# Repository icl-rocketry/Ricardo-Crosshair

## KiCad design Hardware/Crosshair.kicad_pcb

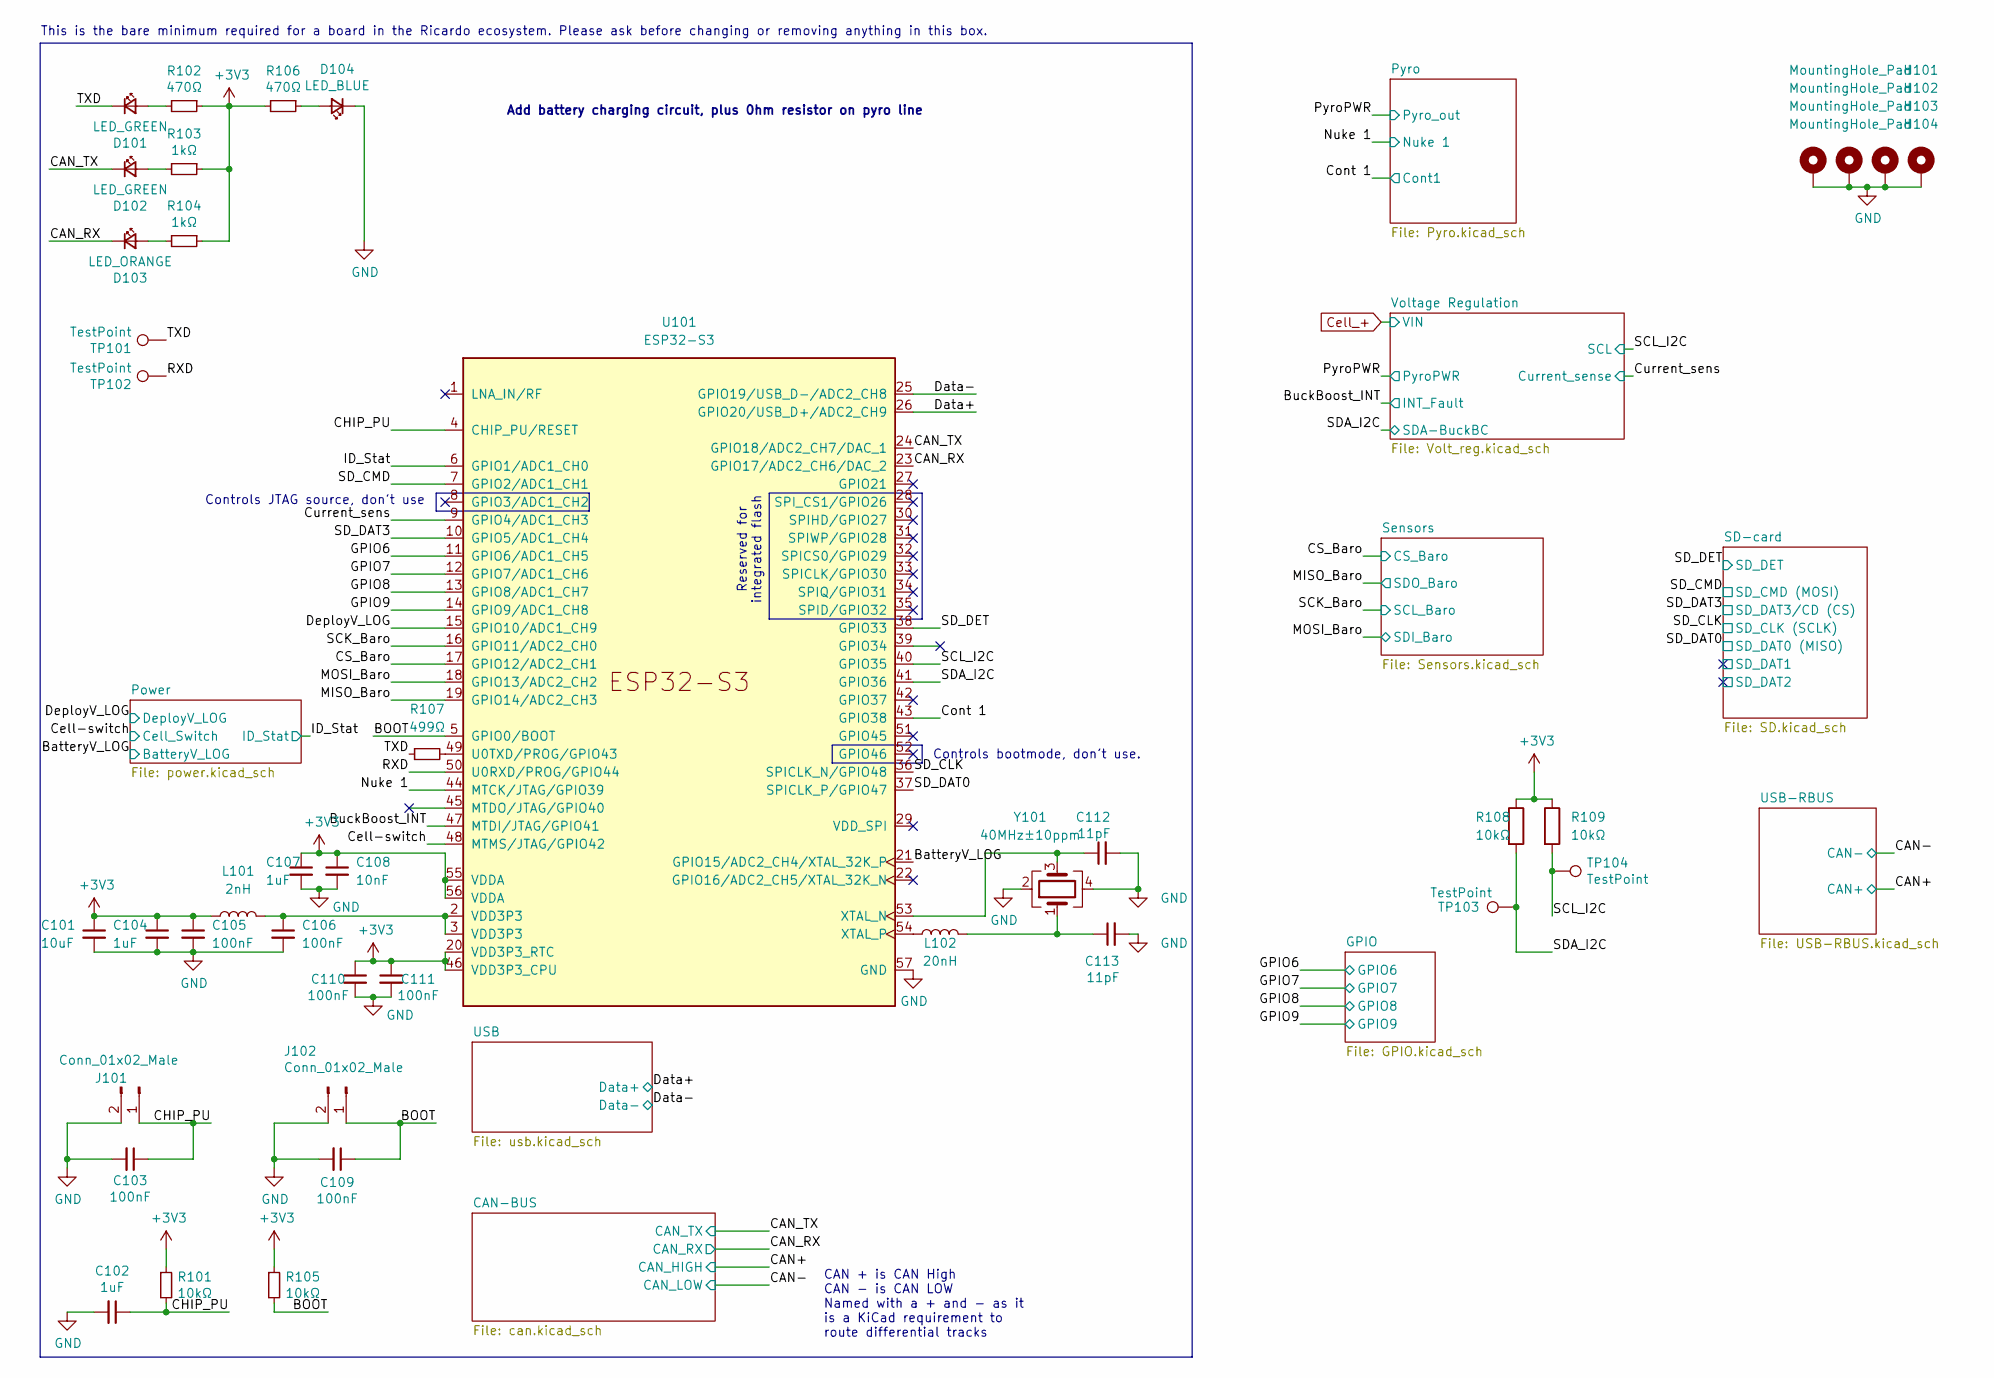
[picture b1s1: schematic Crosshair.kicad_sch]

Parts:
C101: 10uF; C_0402_1005Metric
C102, C104, C107: 1uF; C_0402_1005Metric
C103, C105, C106, C109, C110, C111: 100nF; C_0402_1005Metric
C108: 10nF; C_0402_1005Metric
C112, C113: 11pF; C_0402_1005Metric
D101, D102: LED_GREEN; LED_0402_1005Metric
D103: LED_ORANGE; LED_0402_1005Metric
D104: LED_BLUE; LED_0402_1005Metric
H101, H102, H103, H104: MountingHole_Pad; MountingHole_3.2mm_M3_DIN965_Pad
J101, J102: Conn_01x02_Male; PinHeader_1x02_P2.54mm_Vertical
L101: 2nH; L_0402_1005Metric
L102: 20nH; L_0402_1005Metric
R101, R105, R108, R109: 10kΩ; R_0402_1005Metric
R102, R106: 470Ω; R_0402_1005Metric
R103, R104: 1kΩ; R_0402_1005Metric
R107: 499Ω; R_0402_1005Metric
TP101, TP102, TP103, TP104: TestPoint; TestPoint_Pad_D1.0mm
U101: ESP32-S3; QFN40P700X700X90-57N
Y101: 40MHz±10ppm; Crystal_SMD_2016-4Pin_2.0x1.6mm; MPN R940000171

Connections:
+3V3: C101.1, C104.1, C105.1, C107.1, C108.1, C110.1, C111.1, L101.1, R101.1, R102.1, R103.1, R104.1, R105.1, R106.2, R108.1, R109.1, U101.20 (VDD3P3_RTC), U101.46 (VDD3P3_CPU), U101.55 (VDDA), U101.56 (VDDA); also elsewhere on the board
/BOOT: C109.1, J102.1, R105.2, U101.5 (GPIO0/BOOT)
/BatteryV_LOG: U101.21 (GPIO15/ADC2_CH4/XTAL_32K_P); also elsewhere on the board
/BuckBoost_INT: U101.47 (MTDI/JTAG/GPIO41); also elsewhere on the board
/CAN_RX: D103.1 (K), U101.23 (GPIO17/ADC2_CH6/DAC_2); also elsewhere on the board
/CAN_TX: D102.1 (K), U101.24 (GPIO18/ADC2_CH7/DAC_1); also elsewhere on the board
/CHIP_PU: C102.1, C103.1, J101.1, R101.2, U101.4 (CHIP_PU/RESET)
/CS_Baro: U101.17 (GPIO12/ADC2_CH1); also elsewhere on the board
/Cell-switch: U101.48 (MTMS/JTAG/GPIO42); also elsewhere on the board
/Cont 1: U101.43 (GPIO38); also elsewhere on the board
/Current_sens: U101.9 (GPIO4/ADC1_CH3); also elsewhere on the board
/Data+: U101.26 (GPIO20/USB_D+/ADC2_CH9); also elsewhere on the board
/Data-: U101.25 (GPIO19/USB_D-/ADC2_CH8); also elsewhere on the board
/DeployV_LOG: U101.15 (GPIO10/ADC1_CH9); also elsewhere on the board
/GPIO6: U101.11 (GPIO6/ADC1_CH5); also elsewhere on the board
/GPIO7: U101.12 (GPIO7/ADC1_CH6); also elsewhere on the board
/GPIO8: U101.13 (GPIO8/ADC1_CH7); also elsewhere on the board
/GPIO9: U101.14 (GPIO9/ADC1_CH8); also elsewhere on the board
/ID_Stat: U101.6 (GPIO1/ADC1_CH0); also elsewhere on the board
/MISO_Baro: U101.19 (GPIO14/ADC2_CH3); also elsewhere on the board
/MOSI_Baro: U101.18 (GPIO13/ADC2_CH2); also elsewhere on the board
/Nuke 1: U101.44 (MTCK/JTAG/GPIO39); also elsewhere on the board
/RXD: TP102.1 (1_1), U101.50 (U0RXD/PROG/GPIO44)
/SCK_Baro: U101.16 (GPIO11/ADC2_CH0); also elsewhere on the board
/SCL_I2C: R109.2, TP104.1 (1_1), U101.40 (GPIO35); also elsewhere on the board
/SDA_I2C: R108.2, TP103.1 (1_1), U101.41 (GPIO36); also elsewhere on the board
/SD_CLK: U101.36 (SPICLK_N/GPIO48); also elsewhere on the board
/SD_CMD: U101.7 (GPIO2/ADC1_CH1); also elsewhere on the board
/SD_DAT0: U101.37 (SPICLK_P/GPIO47); also elsewhere on the board
/SD_DAT3: U101.10 (GPIO5/ADC1_CH4); also elsewhere on the board
/SD_DET: U101.38 (GPIO33); also elsewhere on the board
/TXD: D101.1 (K), R107.1, TP101.1 (1_1)
GND: C101.2, C102.2, C103.2, C104.2, C105.2, C106.2, C107.2, C108.2, C109.2, C110.2, C111.2, C112.2, C113.2, D104.1 (K), H101.1 (1_1), H102.1 (1_1), H103.1 (1_1), H104.1 (1_1), J101.2, J102.2, U101.57 (GND), Y101.2, Y101.4; also elsewhere on the board
unnamed: C106.1, L101.2, U101.2 (VDD3P3), U101.3 (VDD3P3)
unnamed: C113.1, L102.2, Y101.1
unnamed: D101.2 (A), R102.2
unnamed: D102.2 (A), R103.2
unnamed: D103.2 (A), R104.2
unnamed: D104.2 (A), R106.1
unnamed: R107.2, U101.49 (U0TXD/PROG/GPIO43)
unnamed: C112.1, U101.53 (XTAL_N), Y101.3
unnamed: L102.1, U101.54 (XTAL_P)

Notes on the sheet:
Controls bootmode, don't use.
This is the bare minimum required for a board in the Ricardo ecosystem. Please ask before changing or removing anything in this box.
CAN + is CAN High CAN - is CAN LOW Named with a + and - as it is a KiCad requirement to route differential tracks
Controls JTAG source, don't use
Add battery charging circuit, plus 0hm resistor on pyro line
Reserved for integrated flash

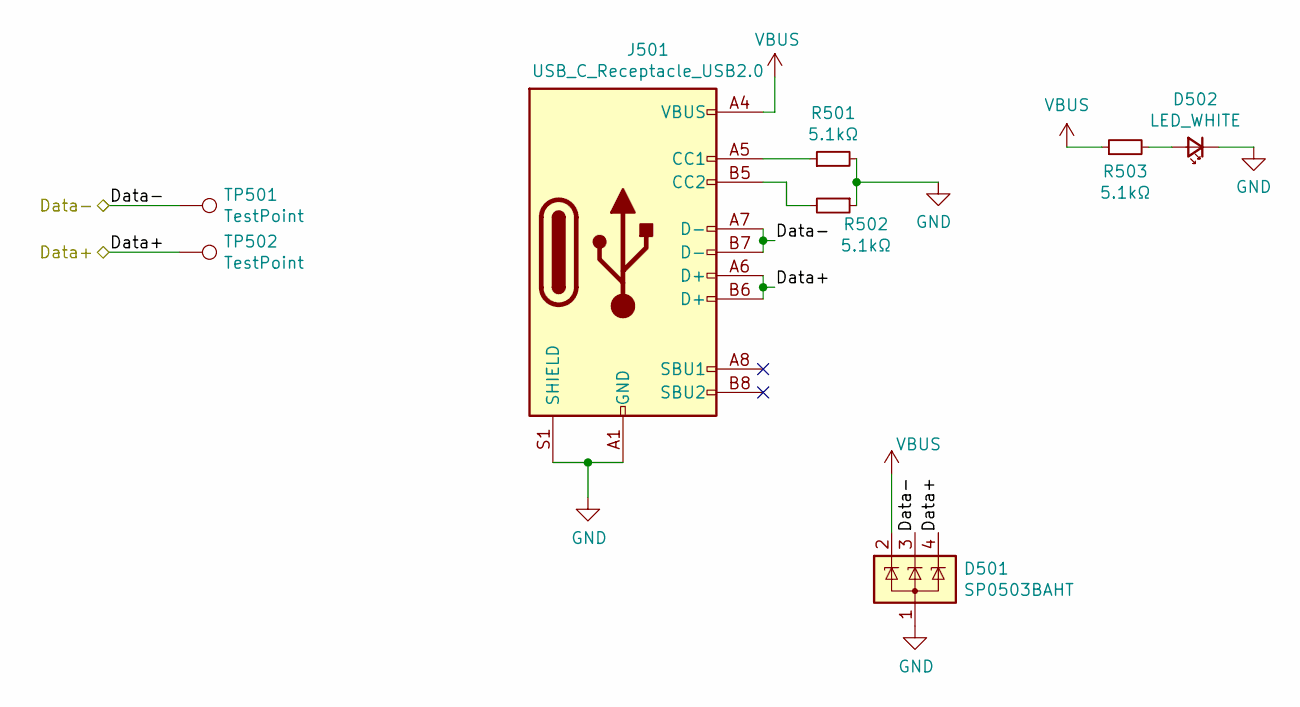
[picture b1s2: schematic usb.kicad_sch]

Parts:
D501: SP0503BAHT; SOT-143
D502: LED_WHITE; LED_0402_1005Metric
J501: USB_C_Receptacle_USB2.0; USB_C_Receptacle_Palconn_UTC16-G
R501, R502, R503: 5.1kΩ; R_0402_1005Metric
TP501, TP502: TestPoint; TestPoint_Pad_D1.0mm

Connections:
/Data+: D501.4 (K), J501.A6 (D+), J501.B6 (D+), TP502.1 (1_1); also elsewhere on the board
/Data-: D501.3 (K), J501.A7 (D-), J501.B7 (D-), TP501.1 (1_1); also elsewhere on the board
GND: D501.1 (A), D502.1 (K), J501.A1 (GND), J501.A12 (GND), J501.B1 (GND), J501.B12 (GND), J501.S1 (SHIELD), R501.2, R502.1; also elsewhere on the board
unnamed: D502.2 (A), R503.2
unnamed: J501.A5 (CC1), R501.1
unnamed: J501.B5 (CC2), R502.2
VBUS: D501.2 (K), J501.A4 (VBUS), J501.A9 (VBUS), J501.B4 (VBUS), J501.B9 (VBUS), R503.1; also elsewhere on the board

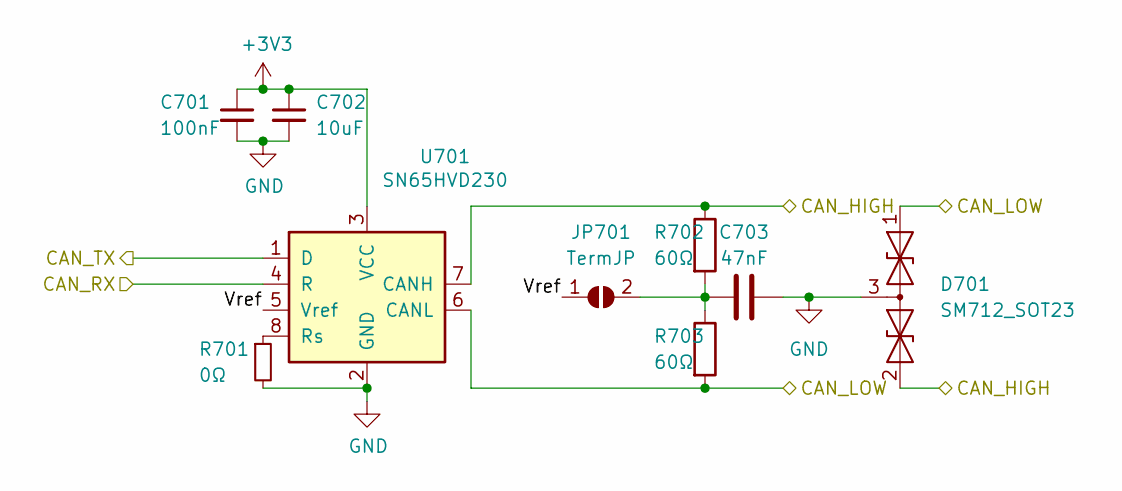
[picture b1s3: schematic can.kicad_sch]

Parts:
C701: 100nF; C_0402_1005Metric
C702: 10uF; C_0402_1005Metric
C703: 47nF; C_0402_1005Metric
D701: SM712_SOT23; SOT-23
JP701: TermJP; SolderJumper-2_P1.3mm_Open_RoundedPad1.0x1.5mm
R701: 0Ω; R_0603_1608Metric
R702, R703: 60Ω; R_0603_1608Metric
U701: SN65HVD230; SOIC-8_3.9x4.9mm_P1.27mm

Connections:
+3V3: C701.1, C702.1, U701.3 (VCC); also elsewhere on the board
/CAN+: D701.2 (A2), R702.1, U701.7 (CANH); also elsewhere on the board
/CAN-: D701.1 (A1), R703.2, U701.6 (CANL); also elsewhere on the board
/CAN-BUS/Vref: JP701.1 (A), U701.5 (Vref)
/CAN_RX: U701.4 (R); also elsewhere on the board
/CAN_TX: U701.1 (D); also elsewhere on the board
GND: C701.2, C702.2, C703.2, D701.3 (common), R701.2, U701.2 (GND); also elsewhere on the board
unnamed: C703.1, JP701.2 (B), R702.2, R703.1
unnamed: R701.1, U701.8 (Rs)

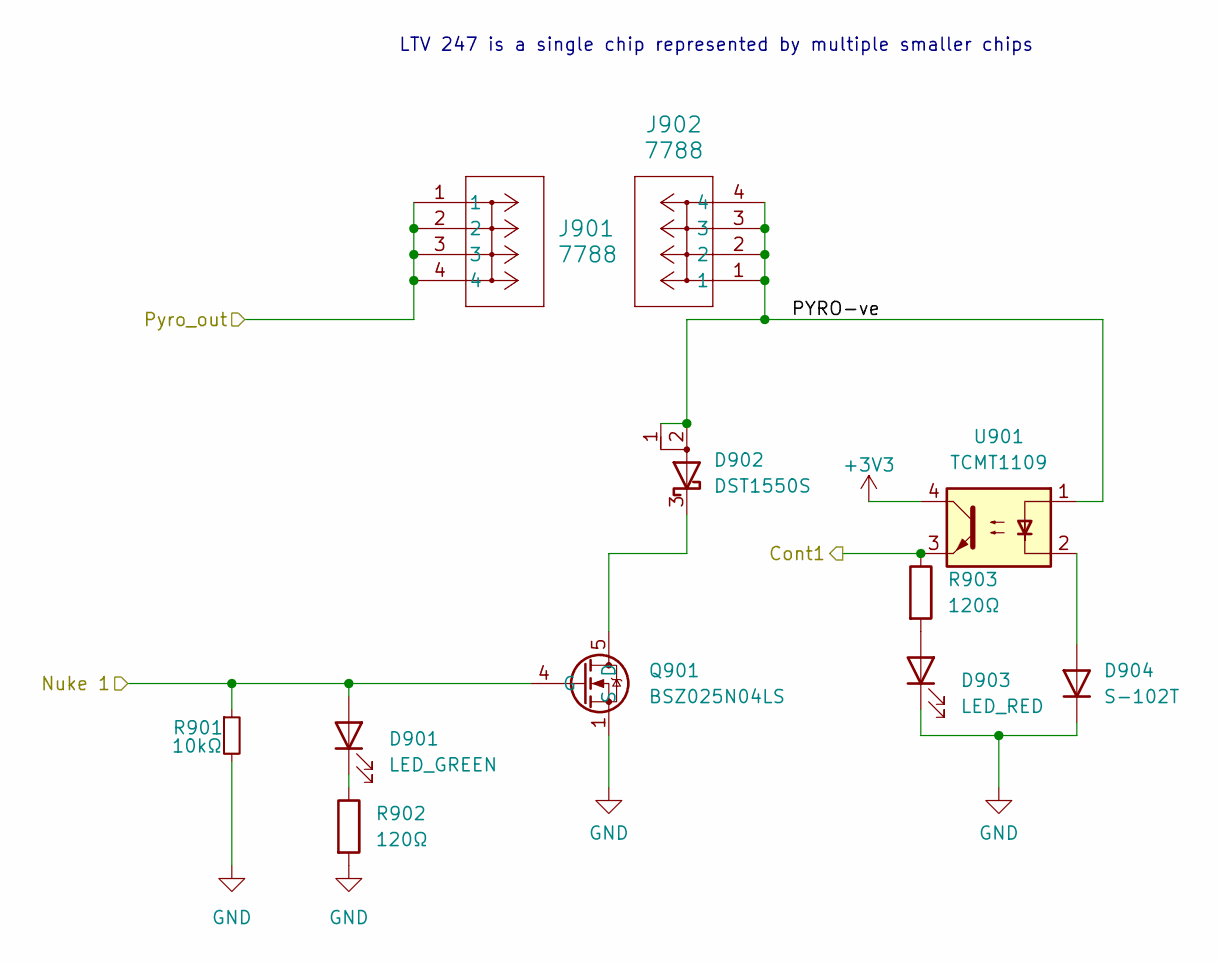
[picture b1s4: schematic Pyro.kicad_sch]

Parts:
D901: LED_GREEN; LED_0402_1005Metric
D902: DST1550S; TO-277B
D903: LED_RED; LED_0603_1608Metric
D904: S-102T; SODFL3516X70N
J901, J902: 7788; CONN_7788_KEY
Q901: BSZ025N04LS; Manufacturer_Part_Number BSZ025N04LS; Mouser Part Number 726-BSZ025N04LS
R901: 10kΩ; R_0402_1005Metric
R902: 120Ω; R_0402_1005Metric
R903: 120Ω; R_0603_1608Metric
U901: TCMT1109; SOP-4_4.4x2.6mm_P1.27mm

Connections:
+3V3: U901.4; also elsewhere on the board
/Cont 1: R903.1, U901.3; also elsewhere on the board
/Nuke 1: D901.2 (A), Q901.4 (G), R901.1; also elsewhere on the board
/Pyro/PYRO-ve: D902.1 (A), D902.2 (A), J902.1, J902.2, J902.3, J902.4, U901.1
/PyroPWR: J901.1, J901.2, J901.3, J901.4; also elsewhere on the board
GND: D903.1 (K), D904.1 (K), Q901.1 (S), Q901.2 (S), Q901.3 (S), Q901.A1 (S), R901.2, R902.2; also elsewhere on the board
unnamed: D901.1 (K), R902.1
unnamed: D902.3 (K), Q901.5 (D), Q901.6 (D), Q901.7 (D), Q901.8 (D), Q901.A5 (D)
unnamed: D903.2 (A), R903.2
unnamed: D904.2 (A), U901.2

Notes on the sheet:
LTV 247 is a single chip represented by multiple smaller chips

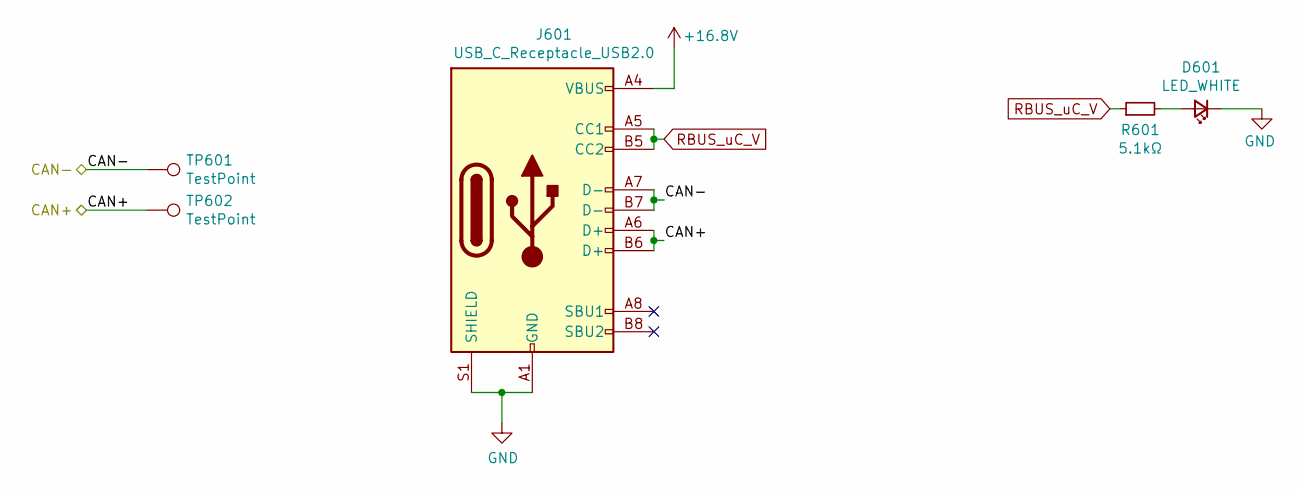
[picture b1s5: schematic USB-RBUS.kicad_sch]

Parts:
D601: LED_WHITE; LED_0402_1005Metric
J601: USB_C_Receptacle_USB2.0; USB_C_Receptacle_Palconn_UTC16-G
R601: 5.1kΩ; R_0402_1005Metric
TP601, TP602: TestPoint; TestPoint_Pad_D1.0mm

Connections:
+16.8V: J601.A4 (VBUS), J601.A9 (VBUS), J601.B4 (VBUS), J601.B9 (VBUS); also elsewhere on the board
/CAN+: J601.A6 (D+), J601.B6 (D+), TP602.1 (1_1); also elsewhere on the board
/CAN-: J601.A7 (D-), J601.B7 (D-), TP601.1 (1_1); also elsewhere on the board
GND: D601.1 (K), J601.A1 (GND), J601.A12 (GND), J601.B1 (GND), J601.B12 (GND), J601.S1 (SHIELD); also elsewhere on the board
unnamed: D601.2 (A), R601.2
RBUS_uC_V: J601.A5 (CC1), J601.B5 (CC2), R601.1; also elsewhere on the board

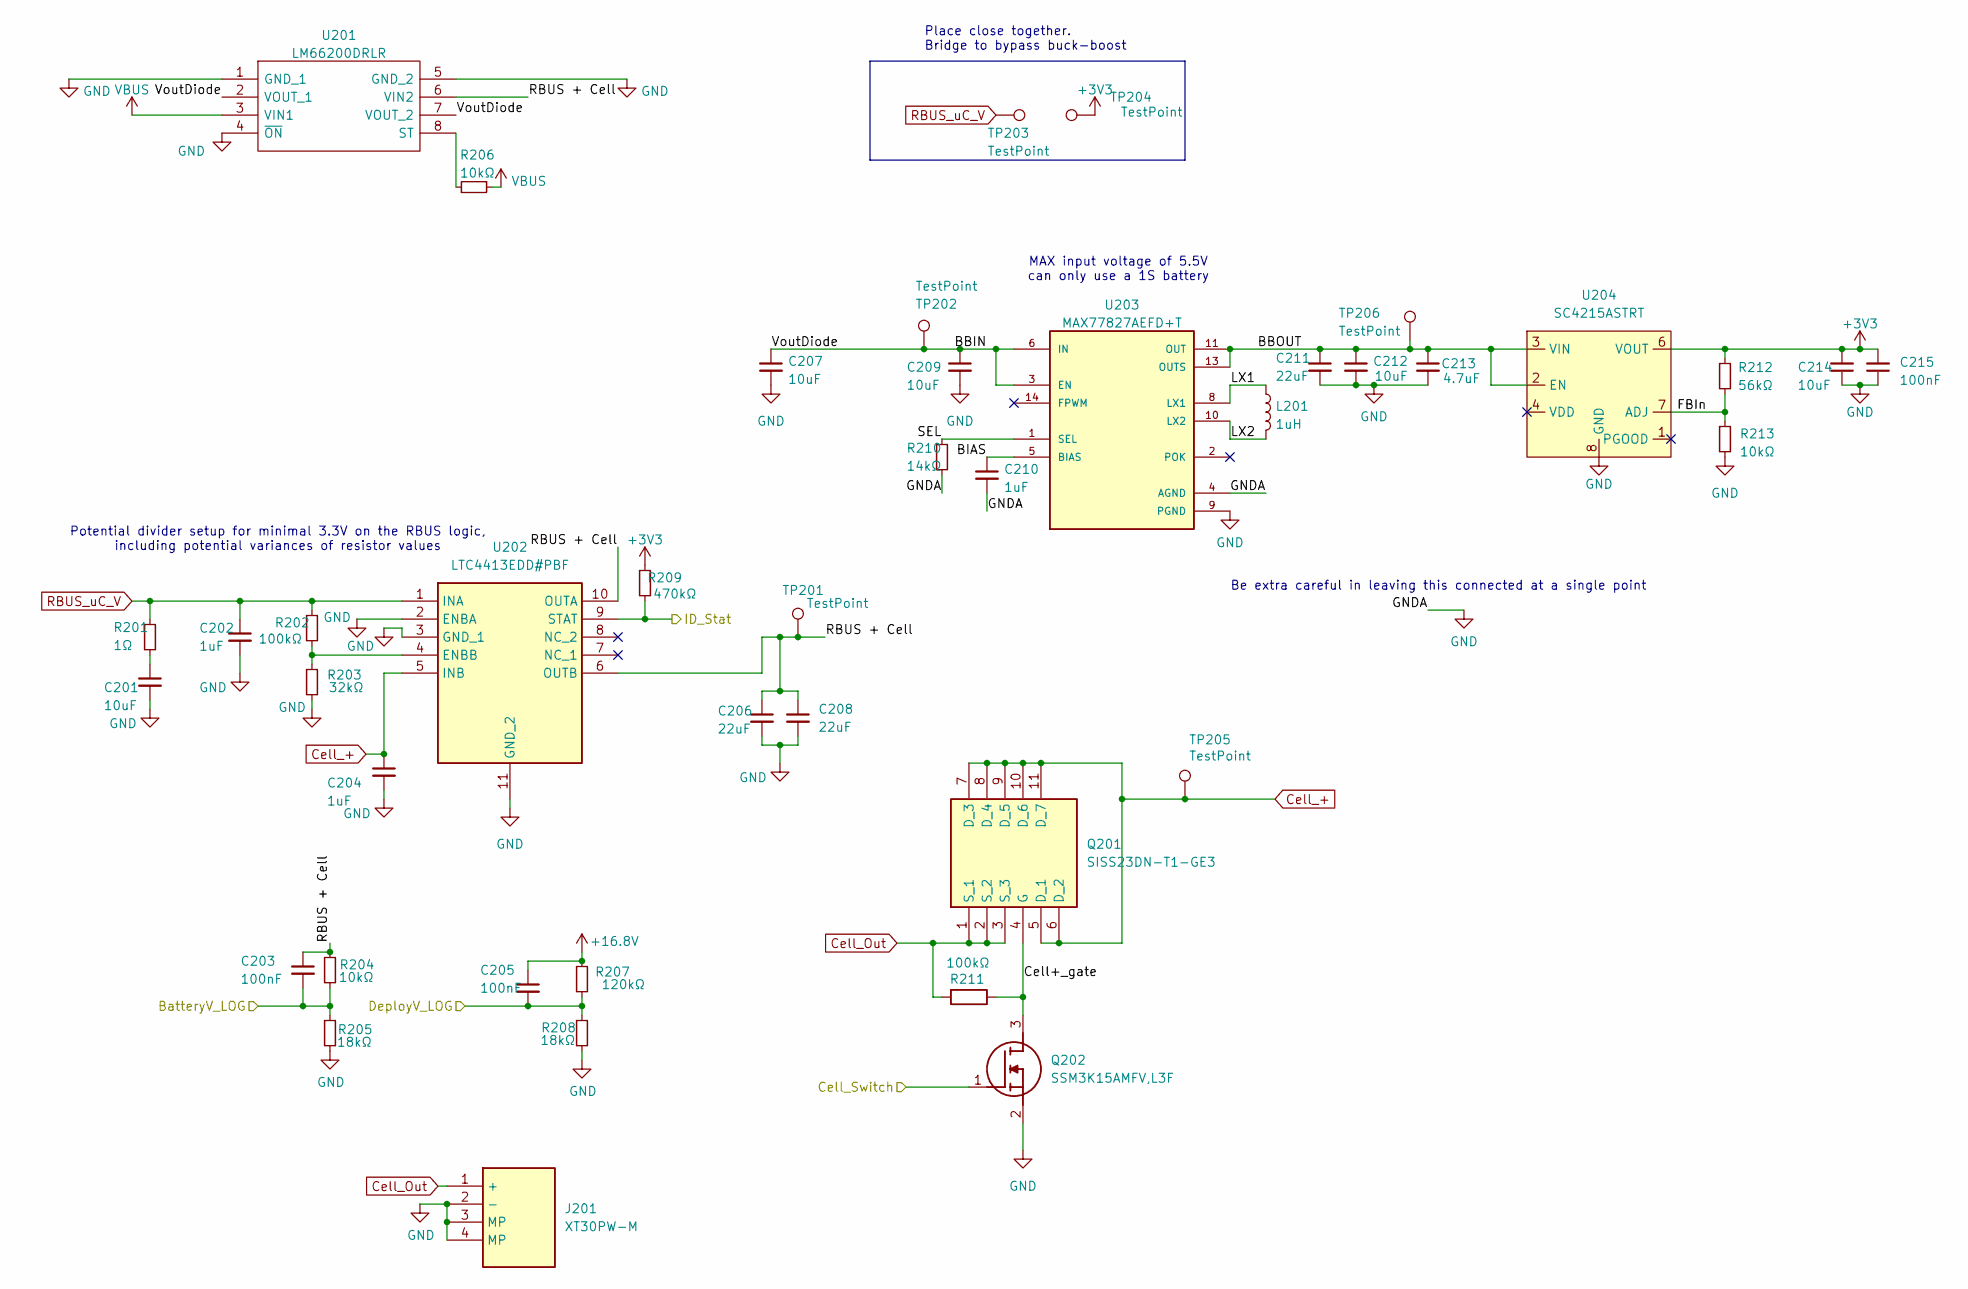
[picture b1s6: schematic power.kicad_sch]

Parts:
C201, C207, C212, C214: 10uF; C_0402_1005Metric
C202, C204, C210: 1uF; C_0402_1005Metric
C203, C205, C215: 100nF; C_0402_1005Metric
C206, C208: 22uF; C_0402_1005Metric
C209: 10uF; C_0603_1608Metric
C211: 22uF; C_0603_1608Metric
C213: 4.7uF; C_0402_1005Metric
J201: XT30PW-M; XT30PWM; Manufacturer_Part_Number XT30PW-M
L201: 1uH; L_0805_2012Metric
Q201: SISS23DN-T1-GE3; SQS850ENT1_GE3; Mouser Part Number 78-SISS23DN-T1-GE3
Q202: SSM3K15AMFV,L3F; SOT-723; Mouser Part Number 757-SSM3K15AMFVL3F
R201: 1Ω; R_0402_1005Metric
R202, R211: 100kΩ; R_0402_1005Metric
R203: 32kΩ; R_0402_1005Metric
R204, R206, R213: 10kΩ; R_0402_1005Metric
R205, R208: 18kΩ; R_0402_1005Metric
R207: 120kΩ; R_0402_1005Metric
R209: 470kΩ; R_0402_1005Metric
R210: 14kΩ; R_0402_1005Metric
R212: 56kΩ; R_0402_1005Metric
TP201: TestPoint; TestPoint_Pad_D1.0mm
TP202, TP203, TP204, TP205, TP206: TestPoint; TestPoint_Pad_D1.5mm
U201: LM66200DRLR; SOTFL50P160X60-8N; Manufacturer_Part_Number LM66200DRLR; Mouser Part Number 595-LM66200DRLR
U202: LTC4413EDD#PBF; SON50P300X300X80-11N-D; Mouser Part Number 584-LTC4413EDD#PBF
U203: MAX77827AEFD+T; CONV_MAX77827AEFD+T; PARTREV B
U204: SC4215ASTRT; SOIC127P599X175-9N

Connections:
+3V3: C214.2, C215.2, R209.1, R212.1, TP204.1 (1_1), U204.6 (VOUT); also elsewhere on the board
+16.8V: C205.1, R207.1; also elsewhere on the board
/BatteryV_LOG: C203.2, R204.2, R205.1; also elsewhere on the board
/Cell-switch: Q202.1 (G); also elsewhere on the board
/DeployV_LOG: C205.2, R207.2, R208.1; also elsewhere on the board
/ID_Stat: R209.2, U202.9 (STAT); also elsewhere on the board
/Power/BBIN: C207.1, C209.1, TP202.1 (1_1), U201.2 (VOUT_1), U201.7 (VOUT_2), U203.3 (EN), U203.6 (IN)
/Power/BBOUT: C211.1, C212.1, C213.1, TP206.1 (1_1), U203.11 (OUT), U203.13 (OUTS), U204.2 (EN), U204.3 (VIN)
/Power/BIAS: C210.1, U203.5 (BIAS)
/Power/Cell+_gate: Q201.4 (G), Q202.3 (D), R211.1
/Power/FBIn: R212.2, R213.1, U204.7 (ADJ)
/Power/LX1: L201.1, U203.8 (LX1)
/Power/LX2: L201.2, U203.10 (LX2)
/Power/RBUS + Cell: C203.1, C206.1, C208.1, R204.1, TP201.1 (1_1), U201.6 (VIN2), U202.6 (OUTB), U202.10 (OUTA)
/Power/SEL: R210.1, U203.1 (SEL)
Cell_+: C204.1, Q201.5 (D_1), Q201.6 (D_2), Q201.7 (D_3), Q201.8 (D_4), Q201.9 (D_5), Q201.10 (D_6), Q201.11 (D_7), TP205.1 (1_1), U202.5 (INB); also elsewhere on the board
Cell_Out: J201.1 (+), Q201.1 (S_1), Q201.2 (S_2), Q201.3 (S_3), R211.2
GND: C201.2, C202.2, C204.2, C206.2, C207.2, C208.2, C209.2, C210.2, C211.2, C212.2, C213.2, C214.1, C215.1, J201.2 (-), J201.3 (MP), J201.4 (MP), Q202.2 (S), R203.2, R205.2, R208.2, R210.2, R213.2, U201.1 (GND_1), U201.4 (~ON), U201.5 (GND_2), U202.2 (ENBA), U202.3 (GND_1), U202.11 (GND_2), U203.4 (AGND), U203.9 (PGND), U204.8 (GND), U204.9 (GND); also elsewhere on the board
unnamed: C201.1, R201.2
unnamed: R206.2, U201.8 (ST)
unnamed: R202.2, R203.1, U202.4 (ENBB)
RBUS_uC_V: C202.1, R201.1, R202.1, TP203.1 (1_1), U202.1 (INA); also elsewhere on the board
VBUS: R206.1, U201.3 (VIN1); also elsewhere on the board

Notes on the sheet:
Place close together. Bridge to bypass buck-boost
MAX input voltage of 5.5V can only use a 1S battery
Potential divider setup for minimal 3.3V on the RBUS logic, including potential variances of resistor values
Be extra careful in leaving this connected at a single point

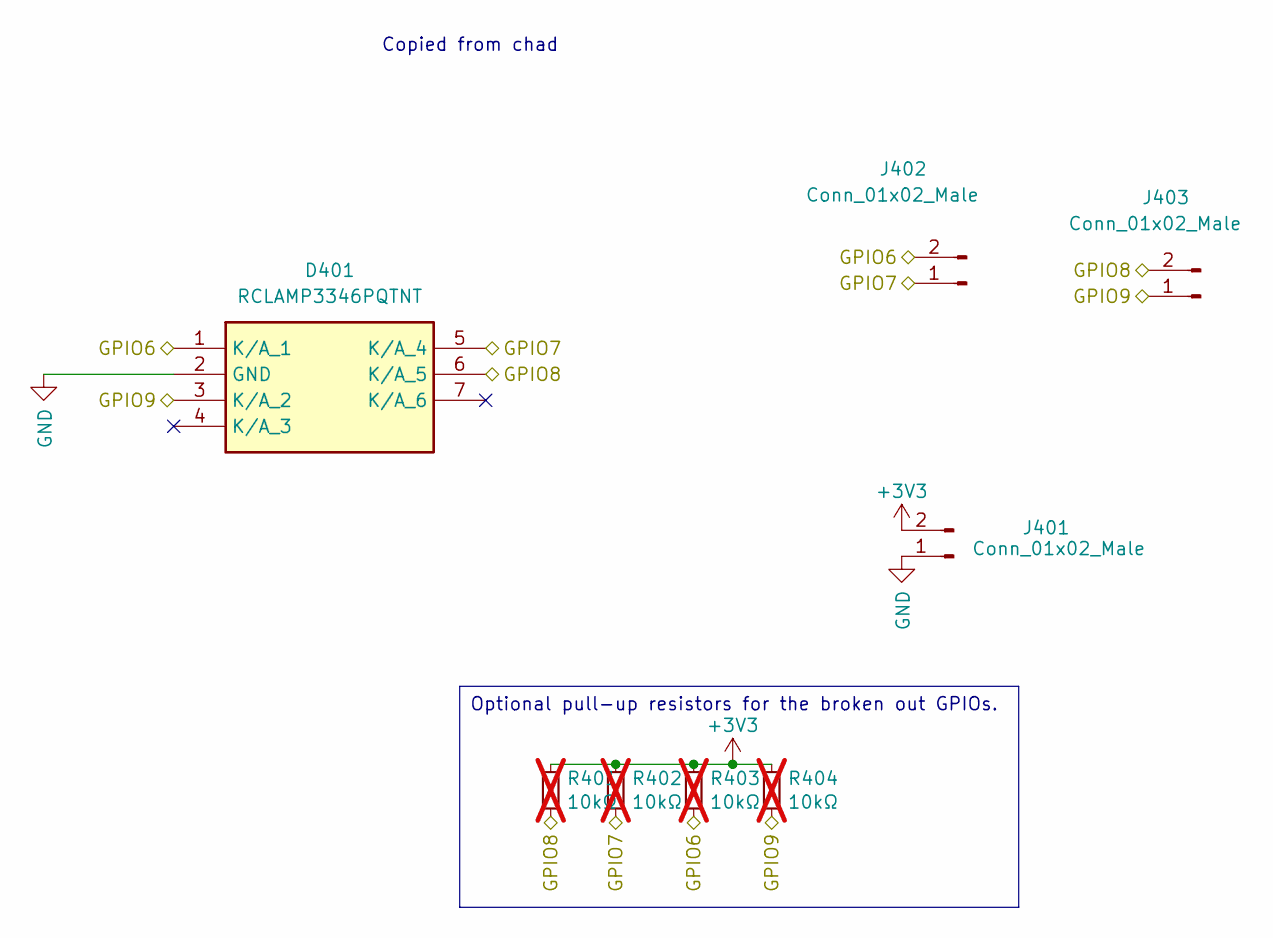
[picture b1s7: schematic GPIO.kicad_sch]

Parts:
D401: RCLAMP3346PQTNT; Mouser Part Number 947-RCLAMP3346PQTNT
J401, J402, J403: Conn_01x02_Male; PinHeader_1x02_P2.54mm_Vertical
R401, R402, R403, R404: 10kΩ; R_0402_1005Metric; not fitted

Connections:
+3V3: J401.2, R401.1, R402.1, R403.1, R404.1; also elsewhere on the board
/GPIO6: D401.1 (K/A_1), J402.2, R403.2; also elsewhere on the board
/GPIO7: D401.5 (K/A_4), J402.1, R402.2; also elsewhere on the board
/GPIO8: D401.6 (K/A_5), J403.2, R401.2; also elsewhere on the board
/GPIO9: D401.3 (K/A_2), J403.1, R404.2; also elsewhere on the board
GND: D401.2 (GND), J401.1; also elsewhere on the board

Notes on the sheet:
Copied from chad
Optional pull-up resistors for the broken out GPIOs.

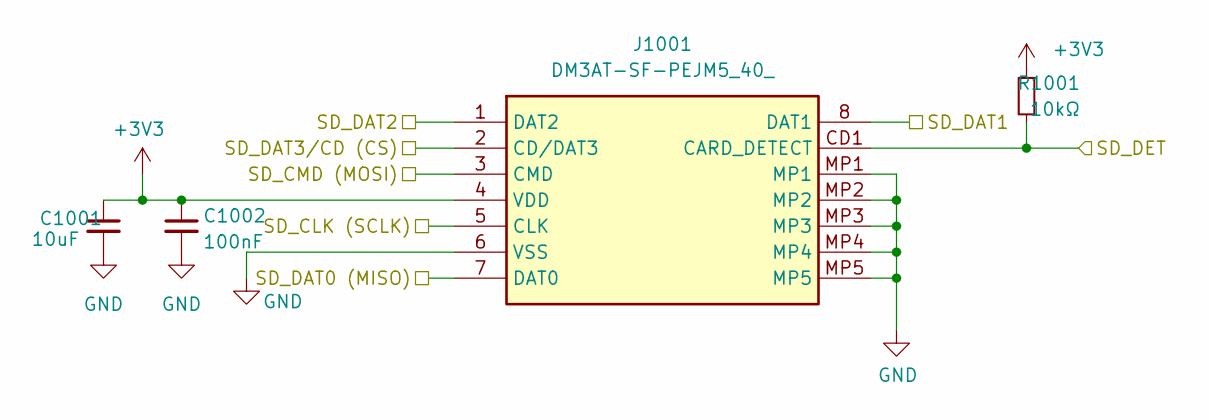
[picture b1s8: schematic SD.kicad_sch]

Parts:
C1001: 10uF; C_0402_1005Metric
C1002: 100nF; C_0402_1005Metric
J1001: DM3AT-SF-PEJM5_40_; DM3ATSFPEJM540; Mouser Part Number 798-DM3AT-SF-PEJM540
R1001: 10kΩ; R_0402_1005Metric

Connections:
+3V3: C1001.1, C1002.1, J1001.4 (VDD), R1001.1; also elsewhere on the board
/SD-card/SD_DAT1: J1001.8 (DAT1)
/SD-card/SD_DAT2: J1001.1 (DAT2)
/SD_CLK: J1001.5 (CLK); also elsewhere on the board
/SD_CMD: J1001.3 (CMD); also elsewhere on the board
/SD_DAT0: J1001.7 (DAT0); also elsewhere on the board
/SD_DAT3: J1001.2 (CD/DAT3); also elsewhere on the board
/SD_DET: J1001.CD1 (CARD_DETECT), R1001.2; also elsewhere on the board
GND: C1001.2, C1002.2, J1001.6 (VSS), J1001.MP1, J1001.MP2, J1001.MP3, J1001.MP4, J1001.MP5; also elsewhere on the board

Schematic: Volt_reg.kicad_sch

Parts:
C301: 180uF; CP_EIA-7260-20_AVX-M
C302, C305: 22uF; C_0805_2012Metric
C303: 82uF; CP_EIA-6032-28_Kemet-C
C304: 10nF; C_0402_1005Metric
C306, C307, C311: 100nF; C_0402_1005Metric
C308: 4.7uF; C_0402_1005Metric
C309: 1.2nF; C_0402_1005Metric
C310: 15pF; C_0402_1005Metric
JP301: CDC; C_0402_1005Metric_Pad0.74x0.62mm_HandSolder
L301: 4.7uH; PA5432472NLT; MPN PA5432472NLT
LED301: LED_RED; LED_0402_1005Metric
Q301, Q302: BSZ025N04LS; Manufacturer_Part_Number BSZ025N04LS; Mouser Part Number 726-BSZ025N04LS
R301: 10mΩ; R_1206_3216Metric
R302: 178kΩ; R_0402_1005Metric
R303: 100kΩ; R_0402_1005Metric
R304: 6.19kΩ; R_0402_1005Metric
R305: 3kΩ; R_0402_1005Metric
R306: 49.9kΩ; R_0402_1005Metric
R307, R308: 10Ω; R_0402_1005Metric
R309: 56kΩ; R_0402_1005Metric
R310: 160kΩ; R_0402_1005Metric
U301: TPS55288QRPMRQ1; TPS552882QRPMRQ1; Mouser Part Number 595-TPS55288QRPMRQ1

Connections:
/BuckBoost_INT: U301.14 (FB/~INT); also elsewhere on the board
/Current_sens: C311.2, JP301.2 (B); also elsewhere on the board
/PyroPWR: R301.2, R305.1, U301.13 (ISN_1), U301.29 (ISN_2); also elsewhere on the board
/SCL_I2C: U301.5 (SCL); also elsewhere on the board
/SDA_I2C: U301.6 (SDA); also elsewhere on the board
/Voltage Regulation/CDC: JP301.1 (A), U301.16 (CDC)
/Voltage Regulation/DITH/SYNC_2: C304.1, U301.7 (DITH/SYNC_1), U301.28 (DITH/SYNC_2)
/Voltage Regulation/DR1L_2: R308.2, U301.1 (DR1L_1), U301.27 (DR1L_2)
/Voltage Regulation/ISP: C303.2, C305.1, R301.1, U301.11 (VOUT_1), U301.12 (ISP), U301.26 (VOUT_2)
/Voltage Regulation/SW2_2: C306.2, L301.2, U301.21 (SW2_1), U301.25 (SW2_2)
/Voltage Regulation/VCC_2: C308.2, U301.19 (VCC_1), U301.30 (VCC_2)
Cell_+: C301.1, C302.2, Q301.5 (D), Q301.6 (D), Q301.7 (D), Q301.8 (D), Q301.A5 (D), R302.1, U301.3 (VIN); also elsewhere on the board
GND: C301.2, C302.1, C303.1, C304.2, C305.2, C308.1, C310.1, C311.1, LED301.1 (K), Q302.1 (S), Q302.2 (S), Q302.3 (S), Q302.A1 (S), R303.2, R304.2, R306.2, R309.1, R310.1, U301.9 (PGND_1), U301.10 (AGND), U301.24 (PGND_2); also elsewhere on the board
unnamed: C309.1, R310.2
unnamed: LED301.2 (A), R305.2
unnamed: Q301.4 (G), R307.1
unnamed: Q302.4 (G), R308.1
unnamed: C307.2, U301.22 (BOOT1)
unnamed: C306.1, U301.20 (BOOT2)
unnamed: C309.2, C310.2, U301.18 (COMP)
unnamed: R307.2, U301.2 (DR1H)
unnamed: R302.2, R303.1, U301.4 (EN/UVLO)
unnamed: R306.1, U301.8 (FSW)
unnamed: R309.2, U301.17 (ILIM)
unnamed: R304.1, U301.15 (MODE)
unnamed: C307.1, L301.1, Q301.1 (S), Q301.2 (S), Q301.3 (S), Q301.A1 (S), Q302.5 (D), Q302.6 (D), Q302.7 (D), Q302.8 (D), Q302.A5 (D), U301.23 (SW1)

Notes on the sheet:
Using (10-bit)DAC program V_ref from 45 mV - 1.2V. Use internal feedback resistor divider by setting FB bit in register 04h to 0. ^ will turn FB/INT pin into internal fault detection pin Write value into the bit CDC [2:0] in register 05h to get the desired voltage compensation(0V by default) for vo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
OUTPUT CURRENT SENSING: V_CDC = 20 × (V_ISP - V_ISN)
Add 8A buck-boost converter, takes VIN outputs into High side switch. 8A: https://www.ti.com/lit/ds/symlink/tps55289.pdf?HQS=dis-mous-null-mousermode-dsf-pf-null-wwe&ts=1738081315650&ref_url=https%253A%252F%252Fwww.mouser.com%252F 16A: https://www.ti.com/lit/ds/slvsf01b/slvsf01b.pdf?ts=173482102789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
Potentially 2.2uH - check!
I2C current sensor uses the same resistor as the current sense for the buckboost

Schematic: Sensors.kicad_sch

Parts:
C801, C802: 100nF; C_0402_1005Metric
U801: DPS368; XDCR_DPS310

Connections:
+3V3: C801.1, C802.1, U801.6 (VDDIO), U801.8 (VDD); also elsewhere on the board
/CS_Baro: U801.2 (~CSB); also elsewhere on the board
/MISO_Baro: U801.5 (SDO); also elsewhere on the board
/MOSI_Baro: U801.3 (SDI); also elsewhere on the board
/SCK_Baro: U801.4 (SCK); also elsewhere on the board
GND: C801.2, C802.2, U801.1 (GND), U801.7 (GND); also elsewhere on the board

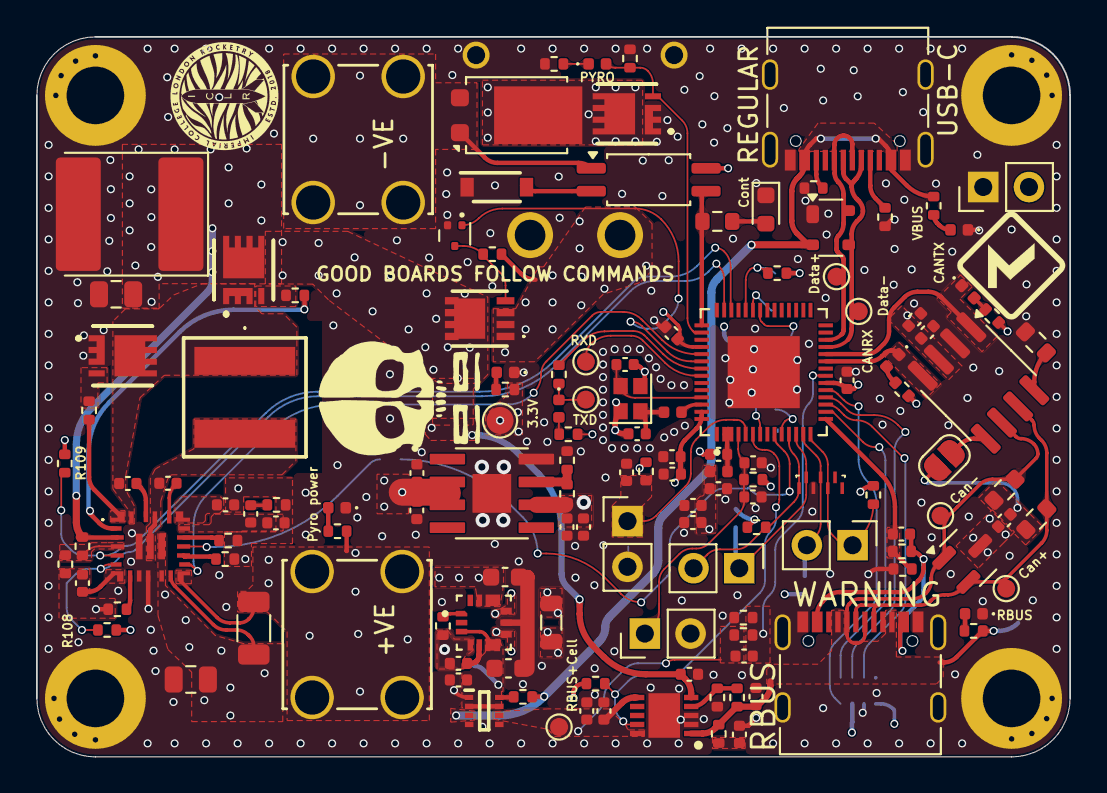
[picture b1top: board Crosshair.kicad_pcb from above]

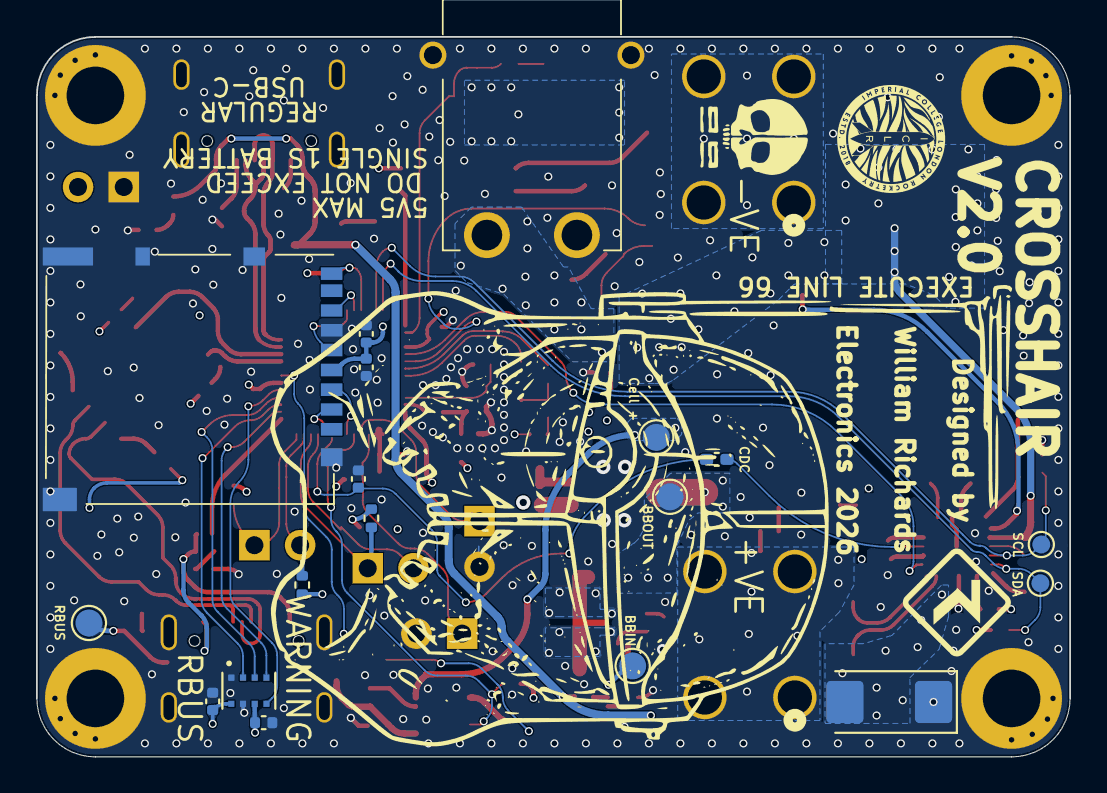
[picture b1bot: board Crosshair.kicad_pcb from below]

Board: 4 copper layers, 57.4 x 40.0 mm, 157 parts (18 on the bottom side), 93 nets.
